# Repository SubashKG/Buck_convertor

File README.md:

View this project on [CADLAB.io](https://cadlab.io/project/29071). 

# Buck_convertor

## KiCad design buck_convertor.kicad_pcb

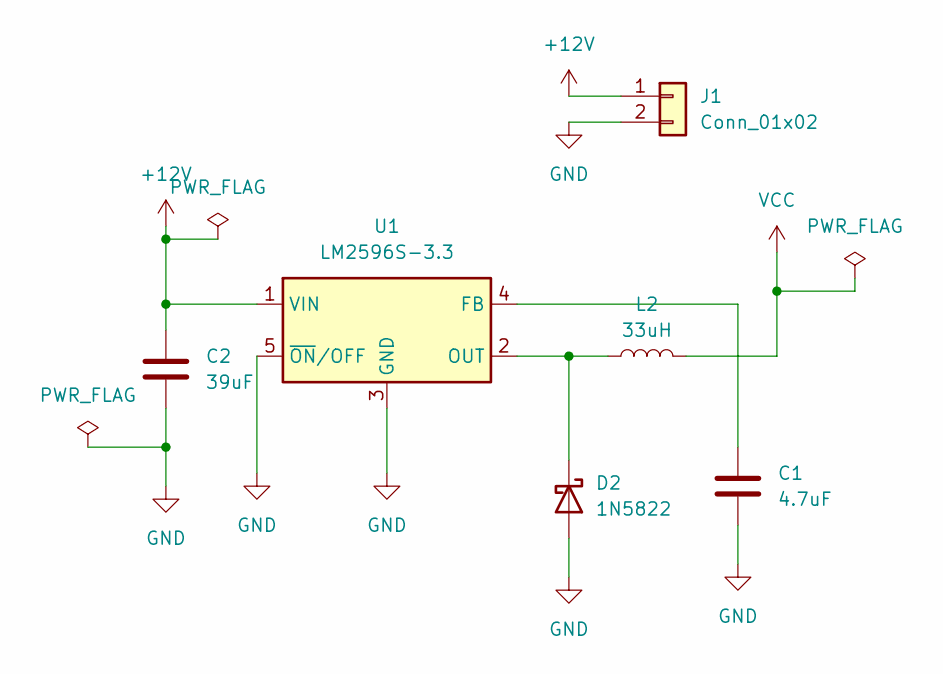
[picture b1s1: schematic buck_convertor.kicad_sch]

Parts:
C1: 4.7uF; CP_Axial_L10.0mm_D4.5mm_P15.00mm_Horizontal
C2: 39uF; CP_Axial_L10.0mm_D4.5mm_P15.00mm_Horizontal
D2: 1N5822; D_DO-201AD_P15.24mm_Horizontal
J1: Conn_01x02; PhoenixContact_MC_1,5_14-GF-3.81_1x14_P3.81mm_Horizontal_Th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
L2: 33uH; L_Radial_D8.7mm_P5.00mm_Fastron_07HCP
U1: LM2596S-3.3; TO-263-5_TabPin3

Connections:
+12V: C2.1, J1.1, U1.1 (VIN)
GND: C1.2, C2.2, D2.2 (A), J1.2, U1.3 (GND), U1.5 (~ON/OFF)
unnamed: D2.1 (K), L2.1, U1.2 (OUT)
unnamed: C1.1, U1.4 (FB)
VCC: L2.2

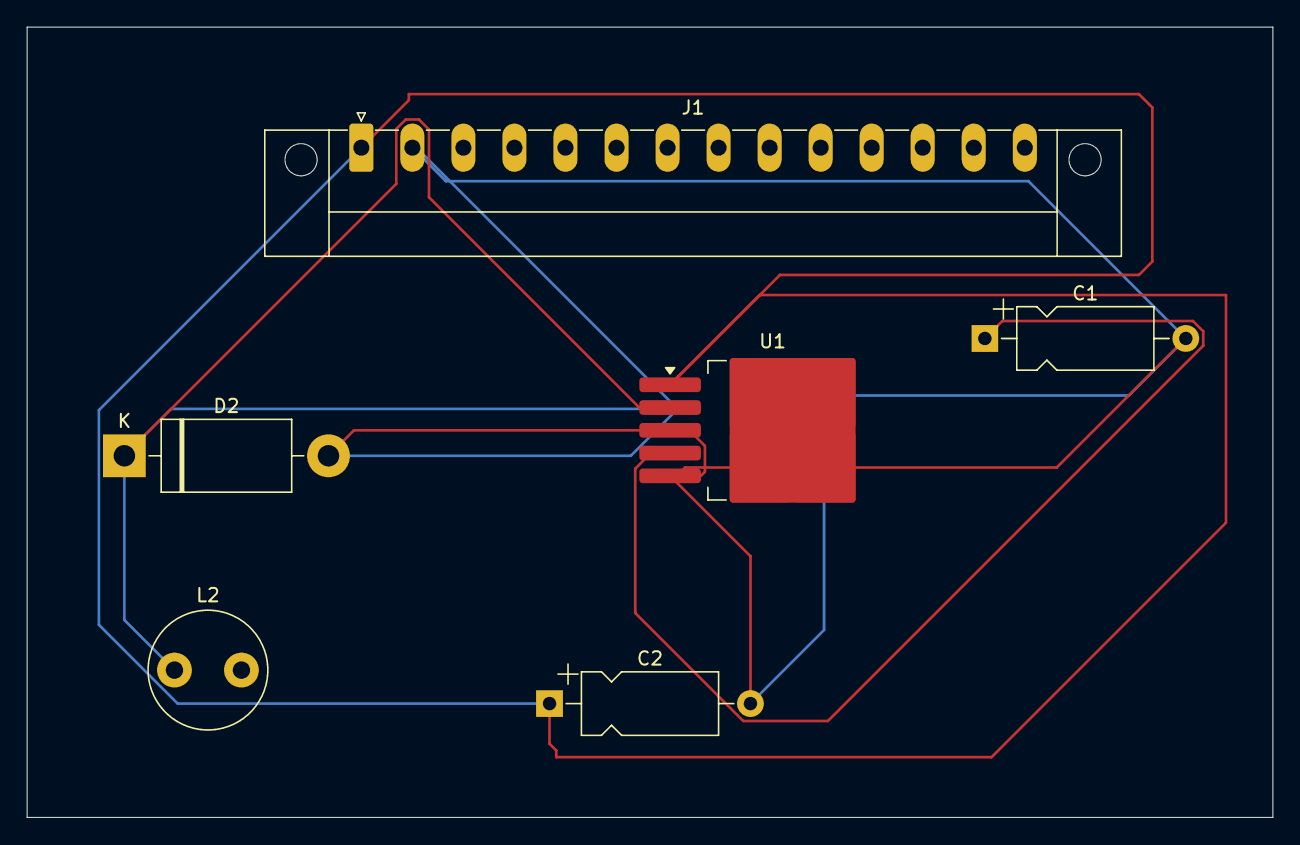
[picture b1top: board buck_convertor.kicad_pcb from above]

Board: 2 copper layers, 93.0 x 59.0 mm, 6 parts (0 on the bottom side), 4 nets.

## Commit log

2025-03-30 Backlink to CADLAB.io has been added.
2025-03-30 Buck convertor
